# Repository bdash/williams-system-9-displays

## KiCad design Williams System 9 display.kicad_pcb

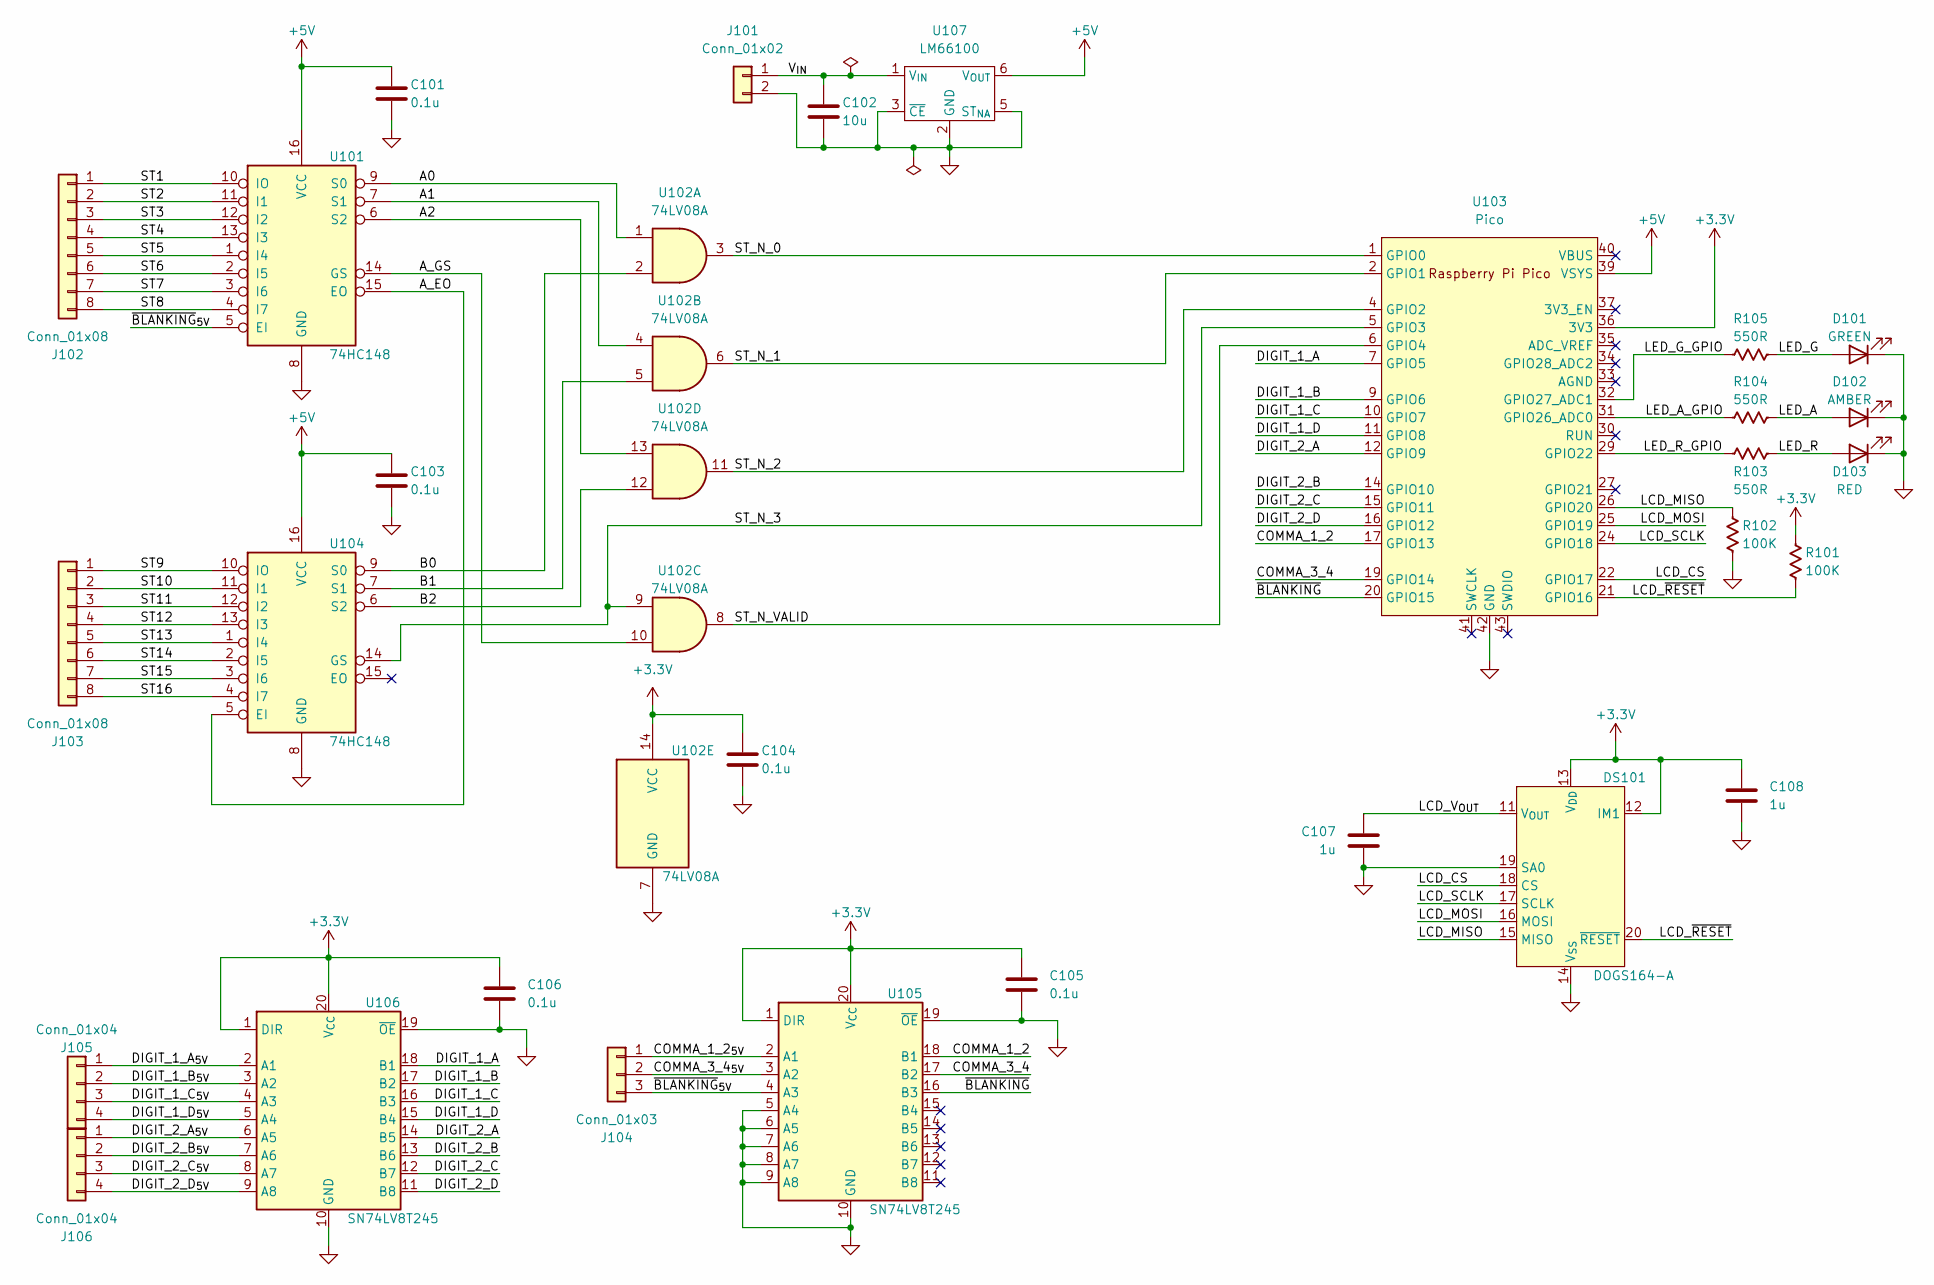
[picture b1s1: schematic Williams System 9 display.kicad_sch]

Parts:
C101, C103, C104, C105, C106: 0.1u; C_0805_2012Metric_Pad1.18x1.45mm_HandSolder
C102: 10u; C_0805_2012Metric_Pad1.18x1.45mm_HandSolder
C107, C108: 1u; C_0805_2012Metric_Pad1.18x1.45mm_HandSolder
D101: GREEN; D_1206_3216Metric_Pad1.42x1.75mm_HandSolder; MPN LTST-C150GKT
D102: AMBER; D_1206_3216Metric_Pad1.42x1.75mm_HandSolder; MPN LTST-C150AKT
D103: RED; D_1206_3216Metric_Pad1.42x1.75mm_HandSolder; MPN LTST-C150EKT
DS101: DOGS164-A; EA_DOGS164X-A
J101: Conn_01x02; PinHeader_1x02_P2.54mm_Vertical
J102, J103: Conn_01x08; PinHeader_1x08_P2.54mm_Vertical
J104: Conn_01x03; PinHeader_1x03_P2.54mm_Vertical
J105, J106: Conn_01x04; PinHeader_1x04_P2.54mm_Vertical
R101, R102: 100K; R_0805_2012Metric_Pad1.15x1.40mm_HandSolder
R103, R104, R105: 550R; R_0805_2012Metric_Pad1.15x1.40mm_HandSolder
U101, U104: 74HC148; DIP-16_W7.62mm; MPN SN74HC148N
U102: 74LV08A; TSSOP-14_4.4x5mm_P0.65mm; MPN 74LV08AT14-13
U103: Pico; RPi_Pico_SMD_TH
U105, U106: SN74LV8T245; TSSOP-20_4.4x6.5mm_P0.65mm
U107: LM66100; SOT-363_SC-70-6_Handsoldering

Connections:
+3.3V: C104.1, C105.1, C106.1, C108.1, DS101.12 (IM1), DS101.13 (V_{DD}), R101.1, U102.14 (VCC), U103.36 (3V3), U105.1 (DIR), U105.20 (V_{CC}), U106.1 (DIR), U106.20 (V_{CC})
+5V: C101.1, C103.1, U101.16 (VCC), U103.39 (VSYS), U104.16 (VCC), U107.6 (V_{OUT})
/A0: U101.9 (S0), U102.1
/A1: U101.7 (S1), U102.4
/A2: U101.6 (S2), U102.13
/A_EO: U101.15 (EO), U104.5 (EI)
/A_GS: U101.14 (GS), U102.10
/B0: U102.2, U104.9 (S0)
/B1: U102.5, U104.7 (S1)
/B2: U102.12, U104.6 (S2)
/COMMA_1_2: U103.17 (GPIO13), U105.18 (B1)
/COMMA_1_2_{5V}: J104.1, U105.2 (A1)
/COMMA_3_4: U103.19 (GPIO14), U105.17 (B2)
/COMMA_3_4_{5V}: J104.2, U105.3 (A2)
/DIGIT_1_A: U103.7 (GPIO5), U106.18 (B1)
/DIGIT_1_A_{5V}: J105.1, U106.2 (A1)
/DIGIT_1_B: U103.9 (GPIO6), U106.17 (B2)
/DIGIT_1_B_{5V}: J105.2, U106.3 (A2)
/DIGIT_1_C: U103.10 (GPIO7), U106.16 (B3)
/DIGIT_1_C_{5V}: J105.3, U106.4 (A3)
/DIGIT_1_D: U103.11 (GPIO8), U106.15 (B4)
/DIGIT_1_D_{5V}: J105.4, U106.5 (A4)
/DIGIT_2_A: U103.12 (GPIO9), U106.14 (B5)
/DIGIT_2_A_{5V}: J106.1, U106.6 (A5)
/DIGIT_2_B: U103.14 (GPIO10), U106.13 (B6)
/DIGIT_2_B_{5V}: J106.2, U106.7 (A6)
/DIGIT_2_C: U103.15 (GPIO11), U106.12 (B7)
/DIGIT_2_C_{5V}: J106.3, U106.8 (A7)
/DIGIT_2_D: U103.16 (GPIO12), U106.11 (B8)
/DIGIT_2_D_{5V}: J106.4, U106.9 (A8)
/LCD_CS: DS101.18 (CS), U103.22 (GPIO17)
/LCD_MISO: DS101.15 (MISO), R102.1, U103.26 (GPIO20)
/LCD_MOSI: DS101.16 (MOSI), U103.25 (GPIO19)
/LCD_SCLK: DS101.17 (SCLK), U103.24 (GPIO18)
/LCD_V_{OUT}: C107.1, DS101.11 (V_{OUT})
/LCD_~RESET: DS101.20 (~RESET), R101.2, U103.21 (GPIO16)
/LED_A: D102.2 (A), R104.2
/LED_A_GPIO: R104.1, U103.31 (GPIO26_ADC0)
/LED_G: D101.2 (A), R105.2
/LED_G_GPIO: R105.1, U103.32 (GPIO27_ADC1)
/LED_R: D103.2 (A), R103.2
/LED_R_GPIO: R103.1, U103.29 (GPIO22)
/ST1: J102.1, U101.10 (IO)
/ST2: J102.2, U101.11 (I1)
/ST3: J102.3, U101.12 (I2)
/ST4: J102.4, U101.13 (I3)
/ST5: J102.5, U101.1 (I4)
/ST6: J102.6, U101.2 (I5)
/ST7: J102.7, U101.3 (I6)
/ST8: J102.8, U101.4 (I7)
/ST9: J103.1, U104.10 (IO)
/ST10: J103.2, U104.11 (I1)
/ST11: J103.3, U104.12 (I2)
/ST12: J103.4, U104.13 (I3)
/ST13: J103.5, U104.1 (I4)
/ST14: J103.6, U104.2 (I5)
/ST15: J103.7, U104.3 (I6)
/ST16: J103.8, U104.4 (I7)
/ST_N_0: U102.3, U103.1 (GPIO0)
/ST_N_1: U102.6, U103.2 (GPIO1)
/ST_N_2: U102.11, U103.4 (GPIO2)
/ST_N_3: U102.9, U103.5 (GPIO3), U104.14 (GS)
/ST_N_VALID: U102.8, U103.6 (GPIO4)
/V_{IN}: C102.1, J101.1, U107.1 (V_{IN})
/~BLANKING: U103.20 (GPIO15), U105.16 (B3)
/~BLANKING_{5V}: J104.3, U101.5 (EI), U105.4 (A3)
GND: C101.2, C102.2, C103.2, C104.2, C105.2, C106.2, C107.2, C108.2, D101.1 (K), D102.1 (K), D103.1 (K), DS101.14 (V_{SS}), DS101.19 (SA0), J101.2, R102.2, U101.8 (GND), U102.7 (GND), U103.3 (GND), U103.8 (GND), U103.13 (GND), U103.18 (GND), U103.23 (GND), U103.28 (GND), U103.38 (GND), U103.42 (GND), U104.8 (GND), U105.5 (A4), U105.6 (A5), U105.7 (A6), U105.8 (A7), U105.9 (A8), U105.10 (GND), U105.19 (~OE), U106.10 (GND), U106.19 (~OE), U107.2 (GND), U107.3 (~CE), U107.5 (ST_{NA})

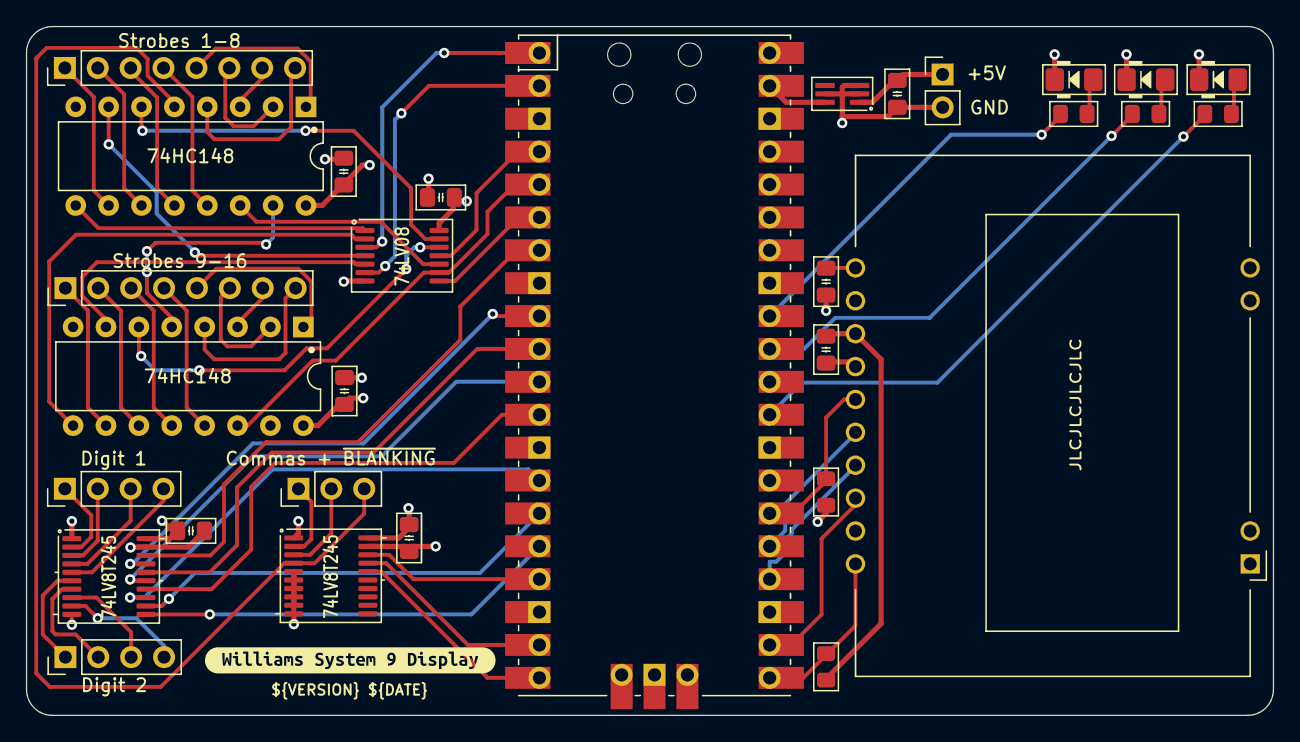
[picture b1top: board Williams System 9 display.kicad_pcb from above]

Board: 4 copper layers, 96.3 x 53.2 mm, 31 parts (0 on the bottom side), 67 nets.

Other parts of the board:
kibuzzard-64FB800B: G***; kibuzzard-64FB800B

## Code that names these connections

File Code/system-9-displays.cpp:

#include "hardware/gpio.h"
#include "pico/binary_info.h"
#include "pico/stdlib.h"
#include <stdio.h>

#include <span>

#include "lcd.h"
#include "pio_spi.h"

const uint LED_PIN = PICO_DEFAULT_LED_PIN;

const uint LCD_RESET_PIN = 16;
const uint LCD_CS_PIN = 17;
const uint LCD_SCLK_PIN = 18;
const uint LCD_MOSI_PIN = 19;
const uint LCD_MISO_PIN = 20;

int main() {
  stdio_init_all();

  gpio_init(LED_PIN);
  gpio_set_dir(LED_PIN, GPIO_OUT);

  gpio_init(LCD_RESET_PIN);
  gpio_put(LCD_RESET_PIN, 1);
  gpio_set_dir(LCD_RESET_PIN, GPIO_OUT);

  // Low pulse > 0.2ms to trigger reset of LCD.
  gpio_put(LCD_RESET_PIN, 0);
  sleep_ms(1);
  gpio_put(LCD_RESET_PIN, 1);

  struct pio_spi_inst lcd_spi = {
      .pio = pio0,
      .sm = 0,
      .cs_pin = LCD_CS_PIN,
  };

  uint prog_offset = pio_add_program(pio0, &spi_program);
  // This is too fast on the breadboard:
  // float clkdiv = 31.25f;  // 1 MHz @ 125 clk_sys
  float clkdiv = 125.f;

  pio_spi_cs_init(lcd_spi.pio, lcd_spi.sm, prog_offset,
                  8 /* bits per SPI frame*/, clkdiv, LCD_CS_PIN, LCD_SCLK_PIN,
                  LCD_MOSI_PIN, LCD_MISO_PIN);

  lcd_init(&lcd_spi);
  uint8_t message[] = "0123456789012345XXXX0123456789012345XXXX0123456789012345"
                      "XXXX0123456789012345";
  lcd_display(&lcd_spi, std::span(message, sizeof(message) - 1));

  while (true) {
    sleep_ms(500);
    message[1]++;
    lcd_set(&lcd_spi, 1, std::span(&message[1], 1));
  }

  return 0;
}

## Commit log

2023-09-08 Initial version, mostly complete
2023-09-08 Make AKL available via personal component library for ease of integration
2023-09-08 Initial attempt at KiBot configuration
2023-09-08 Switch to using a submodule for personal component library
2023-09-08 Address the remaining ERC violations
2023-09-08 Address the remaining DRC violations by updating two footprints to match the library
2023-09-08 Trying using the latest git version of KiBot to see if it can avoid KiCad 7 bugs
2023-09-08 Ensure that GitHub actions check out the components submodules
2023-09-08 Try specifying a container of kicad7_auto_full:dev
2023-09-08 Rounded rect for PCB edge cut
2023-09-08 Disable auto-scaling for pcb_print to work around KiBot exception
2023-09-08 See if caching of 3d models will work
2023-09-08 Re-enable renders that include 3d models of components
2023-09-08 Finish experimenting with better rendering
2023-09-08 More informative silkscreen
2023-09-09 Test whether the use of a container is what is breaking zipping release artifacts
2023-09-09 Upload the JLCPCB outputs rather than OshPark, since that's what I need
2023-09-18 Move LCD functions to separate files
2023-09-18 Group all SPI writes for a packet into a single operation
2023-09-18 Initial version of code that works with real board
    It successfully interprets display data, but output has some tearing and there are occasional errors in displayed values. Both require further investigation.
2023-09-18 Add an LCD class that takes care of initialization
2023-09-18 Hide implementation details using a pimpl-like approach
2023-09-18 Finish adding helpers for LCD packets
2023-09-18 Move toggling of CS into the PIO code for simplicity
2023-09-18 Initial code to demonstrate working the LCD display
2023-09-18 Don't use BLANKING as enable signal for priority encoder since it is of the wrong polarity
2023-09-19 LM66100 should be filled
